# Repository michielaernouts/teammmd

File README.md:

# Ambient Intelligence Project
Team MMD

Members:

Michiel Aernouts, Mats De Meyer, Dennis Joosens

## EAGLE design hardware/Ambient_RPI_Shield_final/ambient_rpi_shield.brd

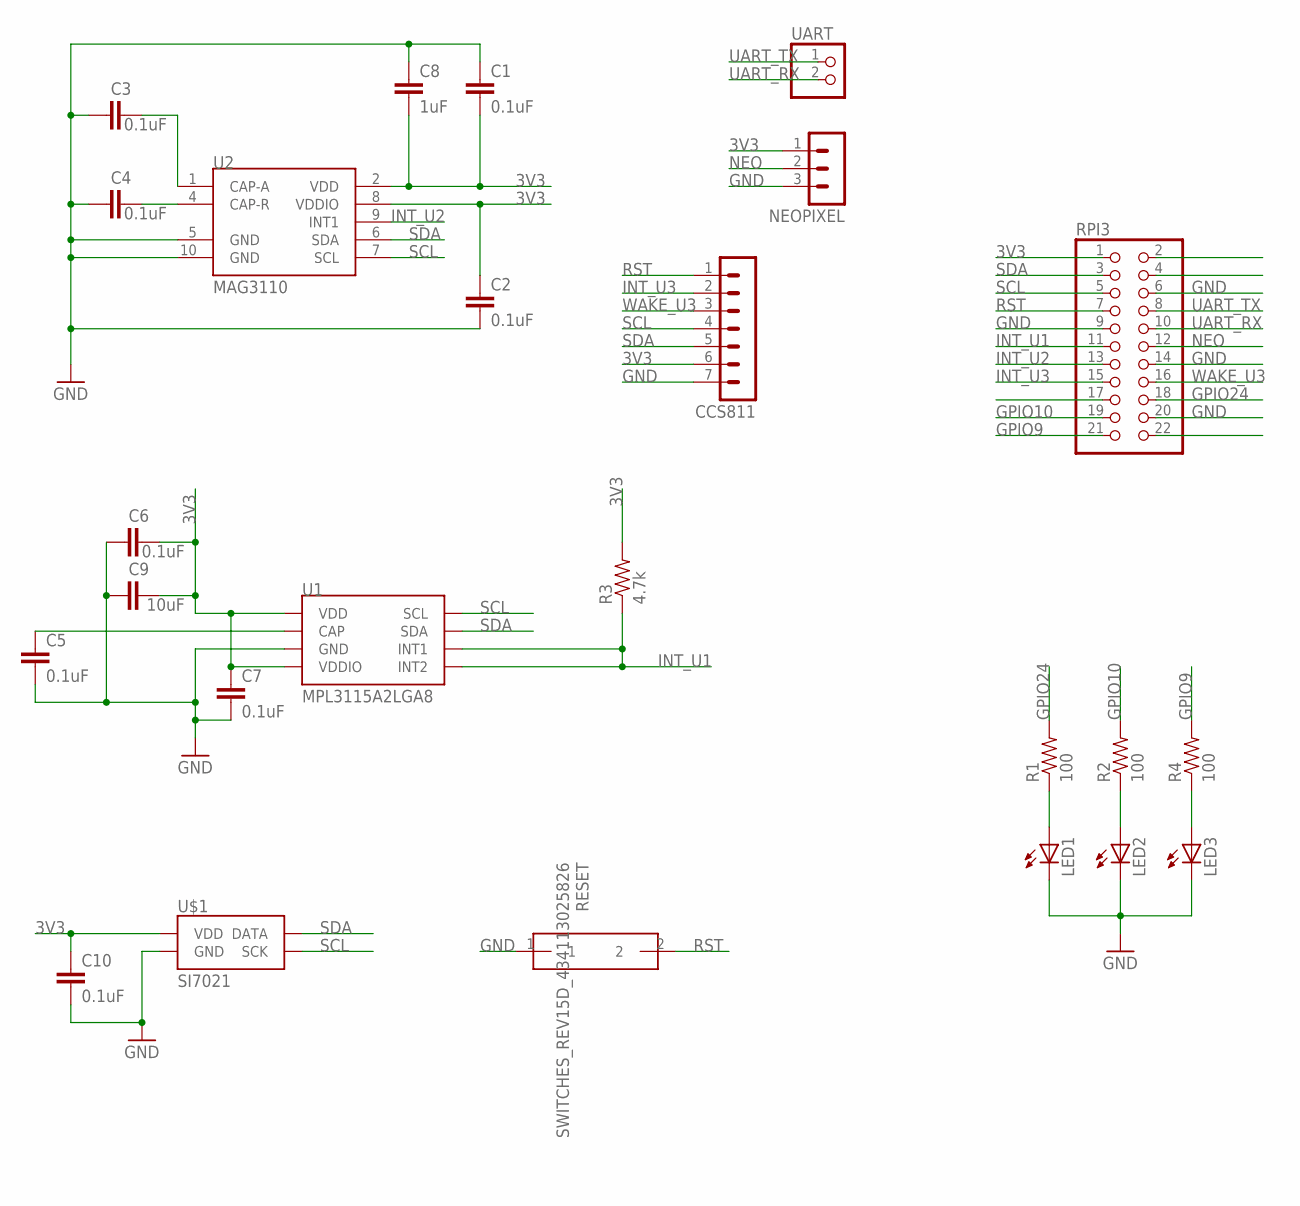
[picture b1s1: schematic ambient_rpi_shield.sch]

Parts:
C1, C2, C3, C4, C5, C6, C7, C10: 0.1uF; 0603-CAP
C8: 1uF; 0603-CAP
C9: 10uF; 0603-CAP
CCS811: MA07-1
LED1, LED2: LED_LEDCHIP-LED0805; LED_CHIP-LED0805
LED3: LED_LEDCHIP-LED0603; LED_CHIP-LED0603
NEOPIXEL: MA03-1
R1, R2, R4: 100; SPARKFUN_0603-RES
R3: 4.7k; 0603-RES
RESET: SWITCHES_REV15D_434113025826
RPI3: PINHD-2X11; 2X11
U1: MPL3115A2LGA8; LGA8
U2: MAG3110; DFN-10
U$1: SI7021
UART: PINHD-1X2; 1X02

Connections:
3V3: C1.2, C2.1, C6.2, C7.1, C8.2, C9.2, C10.1, CCS811.6, NEOPIXEL.1, R3.2, RPI3.1, U1.1 (VDD), U1.4 (VDDIO), U2.2 (VDD), U2.8 (VDDIO), U$1.VDD
GND: C1.1, C2.2, C3.1, C4.1, C5.2, C6.1, C7.2, C8.1, C9.1, C10.2, CCS811.7, LED1.C, LED2.C, LED3.C, NEOPIXEL.3, RESET.1, RPI3.6, RPI3.9, RPI3.14, RPI3.20, U1.3 (GND), U2.5 (GND), U2.10 (GND), U$1.GND
GPIO9: R4.2, RPI3.21
GPIO10: R2.2, RPI3.19
GPIO24: R1.2, RPI3.18
INT_U1: R3.1, RPI3.11, U1.5 (INT2), U1.6 (INT1)
INT_U2: RPI3.13, U2.9 (INT1)
INT_U3: CCS811.2, RPI3.15
unnamed: C3.2, U2.1 (CAP-A)
unnamed: C4.2, U2.4 (CAP-R)
unnamed: C5.1, U1.2 (CAP)
unnamed: LED1.A, R1.1
unnamed: LED2.A, R2.1
unnamed: LED3.A, R4.1
NEO: NEOPIXEL.2, RPI3.12
RST: CCS811.1, RESET.2, RPI3.7
SCL: CCS811.4, RPI3.5, U1.8 (SCL), U2.7 (SCL), U$1.SCK
SDA: CCS811.5, RPI3.3, U1.7 (SDA), U2.6 (SDA), U$1.DATA
UART_RX: RPI3.10, UART.2
UART_TX: RPI3.8, UART.1
WAKE_U3: CCS811.3, RPI3.16

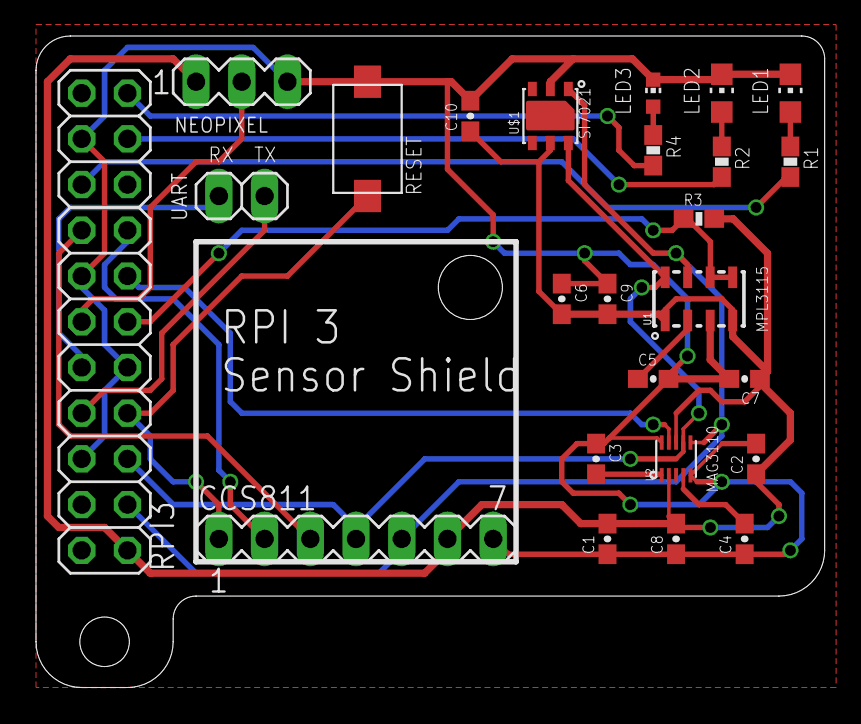
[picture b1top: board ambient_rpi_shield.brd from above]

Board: 2 copper layers, 43.8 x 36.2 mm, 25 parts (0 on the bottom side), 21 nets.

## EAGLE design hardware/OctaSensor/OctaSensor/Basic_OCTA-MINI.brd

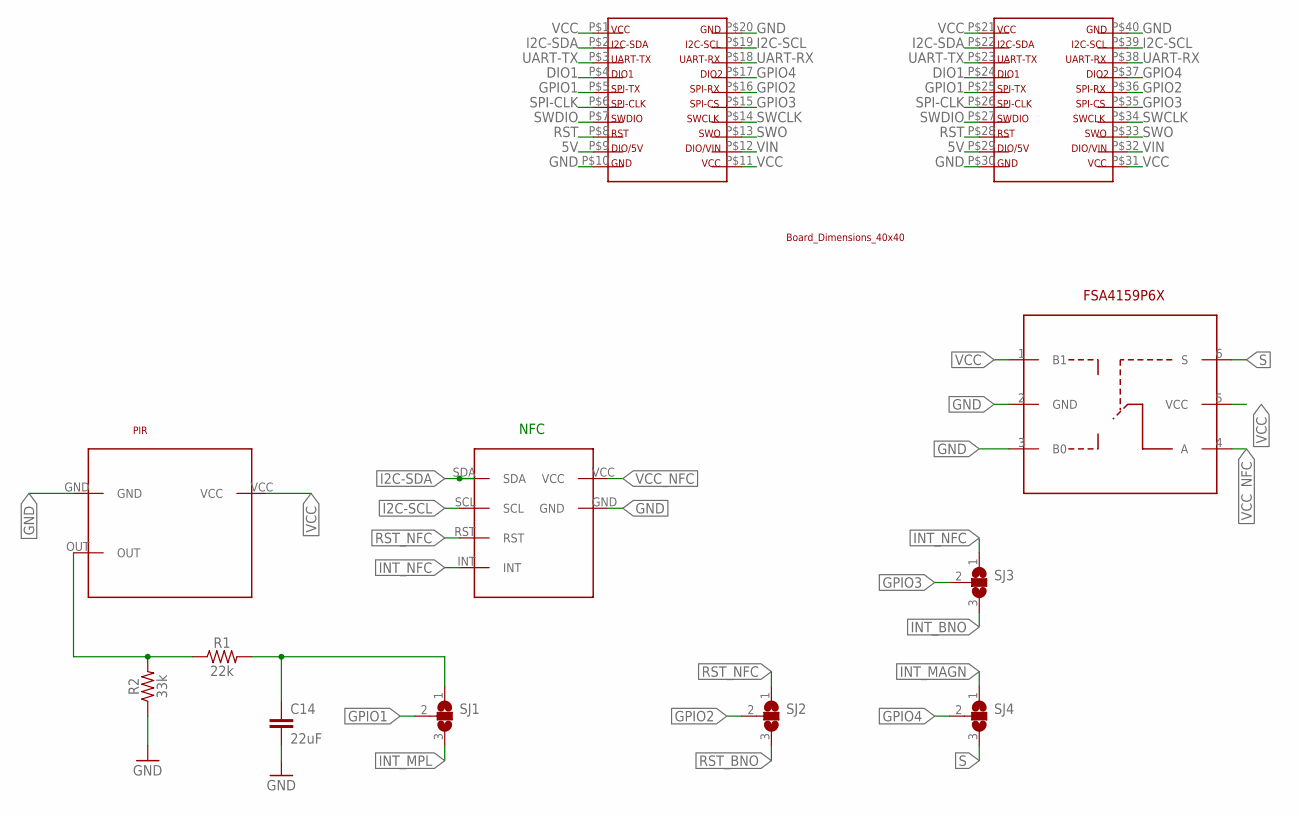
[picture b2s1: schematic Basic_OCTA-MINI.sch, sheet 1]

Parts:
C14: 22uF; 0805
R1: 22k; 0603
R2: 33k; 0603
SJ1, SJ2, SJ3, SJ4: SJ2W; SJ_2
U$2: BOARD-DIMENSIONS-40X40
U$9: PIR
U$10: NFC
U$17: FSA4159P6X; SOT65P210X100-6N

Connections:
5V: U$2.P$9, U$2.P$29
DIO1: U$2.P$4, U$2.P$24
GND: C14.2, R2.1, U$2.P$10, U$2.P$20, U$2.P$30, U$2.P$40, U$9.GND, U$10.GND, U$17.2 (GND), U$17.3 (B0); also elsewhere on the board
GPIO1: SJ1.2, U$2.P$5, U$2.P$25
GPIO2: SJ2.2, U$2.P$16, U$2.P$36
GPIO3: SJ3.2, U$2.P$15, U$2.P$35
GPIO4: SJ4.2, U$2.P$17, U$2.P$37
I2C-SCL: U$2.P$19, U$2.P$39, U$10.SCL; also elsewhere on the board
I2C-SDA: U$2.P$2, U$2.P$22, U$10.SDA; also elsewhere on the board
INT_BNO: SJ3.3; also elsewhere on the board
INT_MAGN: SJ4.1; also elsewhere on the board
INT_MPL: SJ1.3; also elsewhere on the board
INT_NFC: SJ3.1, U$10.INT
unnamed: R1.1, R2.2, U$9.OUT
OUT2_PIR: C14.1, R1.2, SJ1.1
RST: U$2.P$8, U$2.P$28
RST_BNO: SJ2.3; also elsewhere on the board
RST_NFC: SJ2.1, U$10.RST
S: SJ4.3, U$17.6 (S)
SPI-CLK: U$2.P$6, U$2.P$26
SWCLK: U$2.P$14, U$2.P$34
SWDIO: U$2.P$7, U$2.P$27
SWO: U$2.P$13, U$2.P$33
UART-RX: U$2.P$18, U$2.P$38
UART-TX: U$2.P$3, U$2.P$23
VCC: U$2.P$1, U$2.P$11, U$2.P$21, U$2.P$31, U$9.VCC, U$17.1 (B1), U$17.5 (VCC); also elsewhere on the board
VCC_NFC: U$10.VCC, U$17.4 (A)
VIN: U$2.P$12, U$2.P$32

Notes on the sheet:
NFC

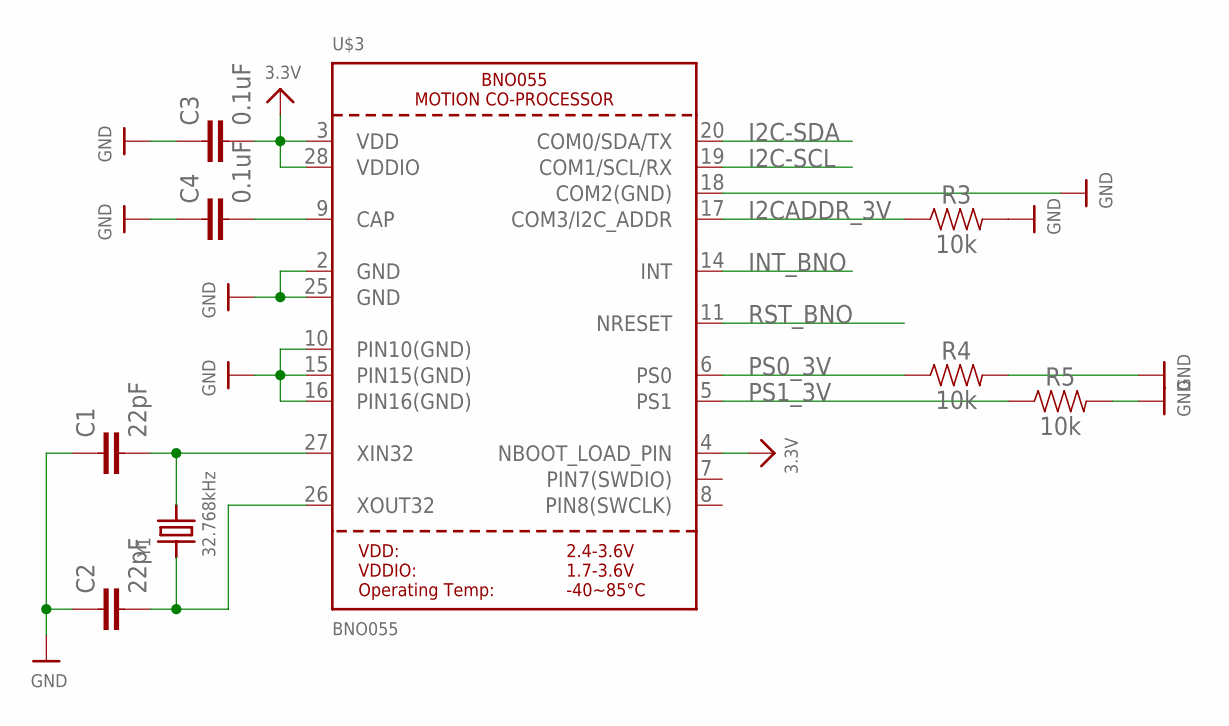
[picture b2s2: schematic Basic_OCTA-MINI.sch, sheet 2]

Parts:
C1, C2: 22pF; 0603
C3, C4: 0.1uF; 0603
R3, R4, R5: 10k; 0603
U$3: BNO055
Y1: 32.768kHz; CRYSTAL_8X3.8

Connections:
GND: C1.1, C2.1, C3.1, C4.1, R3.2, R4.2, R5.2, U$3.2 (GND), U$3.10 (PIN10(GND)), U$3.15 (PIN15(GND)), U$3.16 (PIN16(GND)), U$3.18 (COM2(GND)), U$3.25 (GND); also elsewhere on the board
I2C-SCL: U$3.19 (COM1/SCL/RX); also elsewhere on the board
I2C-SDA: U$3.20 (COM0/SDA/TX); also elsewhere on the board
I2CADDR_3V: R3.1, U$3.17 (COM3/I2C_ADDR)
INT_BNO: U$3.14 (INT); also elsewhere on the board
unnamed: C1.2, U$3.27 (XIN32), Y1.P$4 (2)
unnamed: C2.2, U$3.26 (XOUT32), Y1.P$1 (1)
unnamed: C4.2, U$3.9 (CAP)
PS0_3V: R4.1, U$3.6 (PS0)
PS1_3V: R5.1, U$3.5 (PS1)
RST_BNO: U$3.11 (NRESET); also elsewhere on the board
VCC: C3.2, U$3.3 (VDD), U$3.4 (NBOOT_LOAD_PIN), U$3.28 (VDDIO); also elsewhere on the board

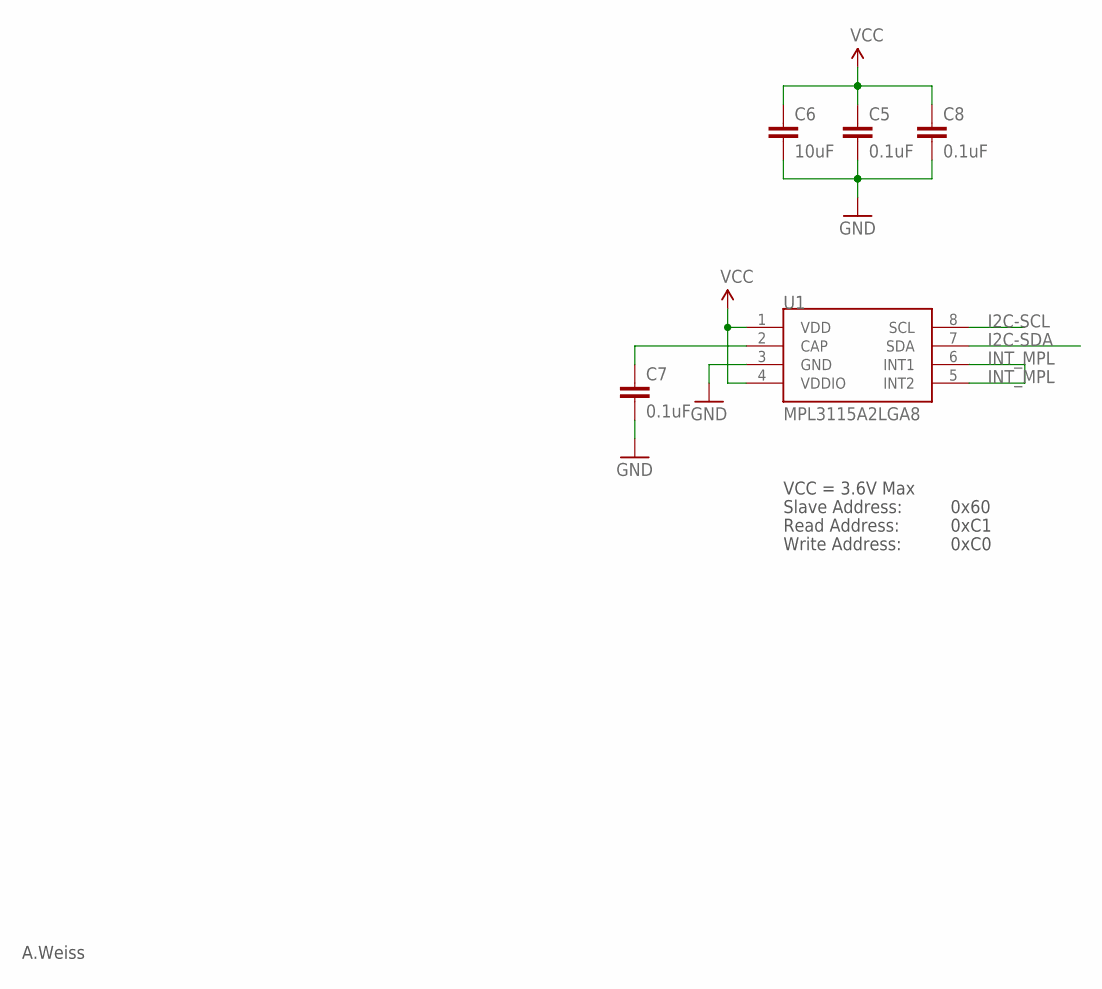
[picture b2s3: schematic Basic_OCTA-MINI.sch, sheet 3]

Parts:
C5, C7, C8: 0.1uF; 0603
C6: 10uF; 0603
U1: MPL3115A2LGA8; LGA8

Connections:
GND: C5.2, C6.2, C7.2, C8.2, U1.3 (GND); also elsewhere on the board
I2C-SCL: U1.8 (SCL); also elsewhere on the board
I2C-SDA: U1.7 (SDA); also elsewhere on the board
INT_MPL: U1.5 (INT2), U1.6 (INT1); also elsewhere on the board
unnamed: C7.1, U1.2 (CAP)
VCC: C5.1, C6.1, C8.1, U1.1 (VDD), U1.4 (VDDIO); also elsewhere on the board

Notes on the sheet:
A.Weiss
VCC = 3.6V Max
Read Address:
Write Address:
Slave Address:
0x60
0xC1
0xC0

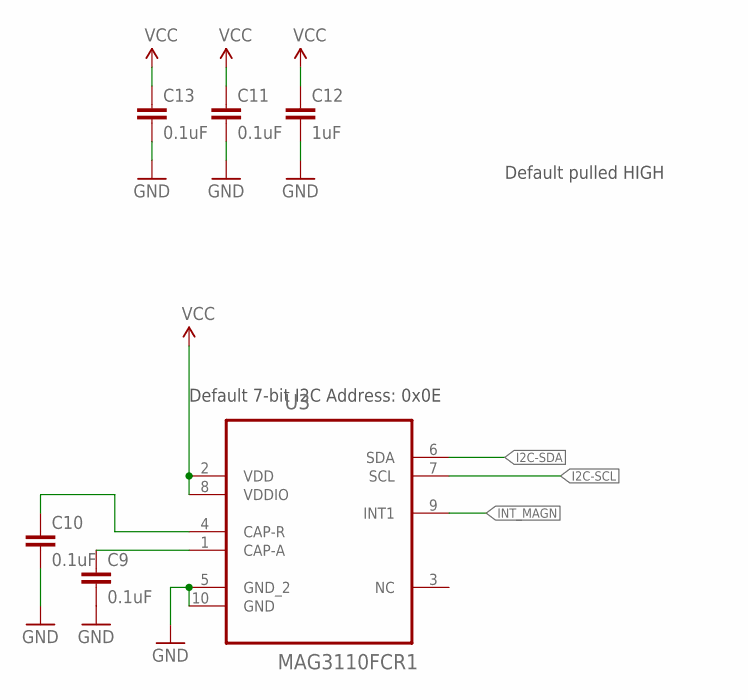
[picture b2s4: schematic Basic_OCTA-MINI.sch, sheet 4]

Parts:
C9, C10, C11, C13: 0.1uF; 0603-CAP
C12: 1uF; 0603-CAP
U3: MAG3110FCR1; DFN200X200X90-10N

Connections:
GND: C9.2, C10.2, C11.2, C12.2, C13.2, U3.5 (GND_2), U3.10 (GND); also elsewhere on the board
I2C-SCL: U3.7 (SCL); also elsewhere on the board
I2C-SDA: U3.6 (SDA); also elsewhere on the board
INT_MAGN: U3.9 (INT1); also elsewhere on the board
unnamed: C10.1, U3.4 (CAP-R)
unnamed: C9.1, U3.1 (CAP-A)
VCC: C11.1, C12.1, C13.1, U3.2 (VDD), U3.8 (VDDIO); also elsewhere on the board

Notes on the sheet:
Default pulled HIGH
Default 7-bit I2C Address: 0x0E

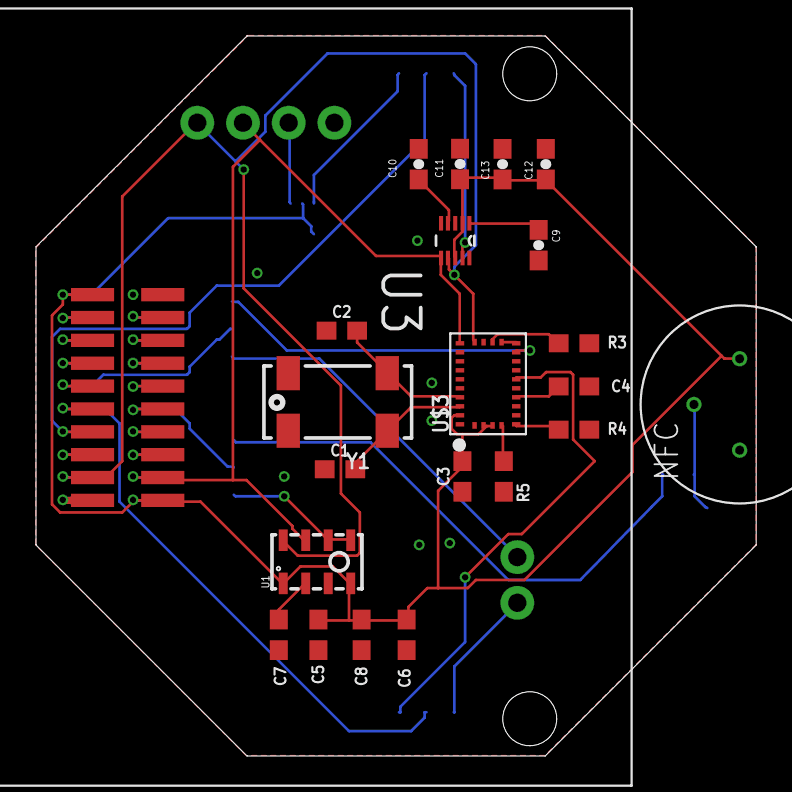
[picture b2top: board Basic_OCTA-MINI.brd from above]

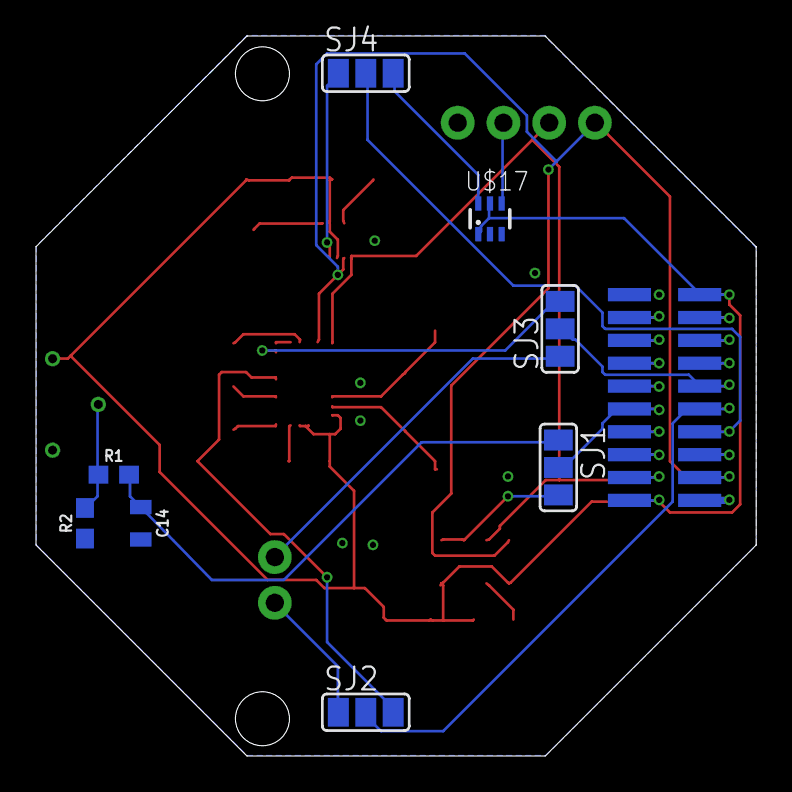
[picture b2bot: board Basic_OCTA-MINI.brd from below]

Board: 2 copper layers, 40.0 x 40.0 mm, 31 parts (8 on the bottom side), 37 nets.

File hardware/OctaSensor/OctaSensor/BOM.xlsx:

Description | Value | Parts | Package | # per board | Ordernummer | Website
Capacitor | 0.1uF | C9, C10, C11, C13,C3, C4, C5, C7 | 0603-CAP | 9 | 1759016 | farnell
1µF ceramic capacitors | 1.0uF | C8,C12 | 0603-CAP | 1 | 1759399 | farnell
10µF ceramic capacitors | 10uF | C6 | 0603-CAP | 1 | 2494233 | farnell
22pF ceramic capacitors | 22pF | C1, C2 | 0603-CAP | 2 | 9406107 | farnell
22µF ceramic capacitors | 22uF | C14 | 8050-CAP | 1 | 1759415 | farnell
33kΩ resistor | 33k | R2 | 0603-CAP | 1 | 2447342 | farnell
10kΩ resistor | 10k | R3, R4, R5 | 0603-CAP | 3 | 2447230 | farnell
22kΩ resistor | 22k | R1 | 0603-CAP | 1 | 2073430 | farnell
Crystals | 32.768kHz | Y1 | CRYSTAL_8X3.8 | 1 | 1611824 | farnell
Analogue Switch | FSA4159P6X | U$17 | SOT65P210X100-6N | 1 | 1495462 | farnell
MAGNETOMETER | MAG3110FCR1 | U3 | DFN200X200X90-10N | 1 | 2080492 | farnell
Altimeter/Pressure Sensor | MPL3115A2LGA8 | U1 | LGA8 | 1 | 2009084 | farnell
BNO055 - Motion Co-Processor | BNO055 | U$3 | BNO055 | 1 | 262-BNO055 | mouser

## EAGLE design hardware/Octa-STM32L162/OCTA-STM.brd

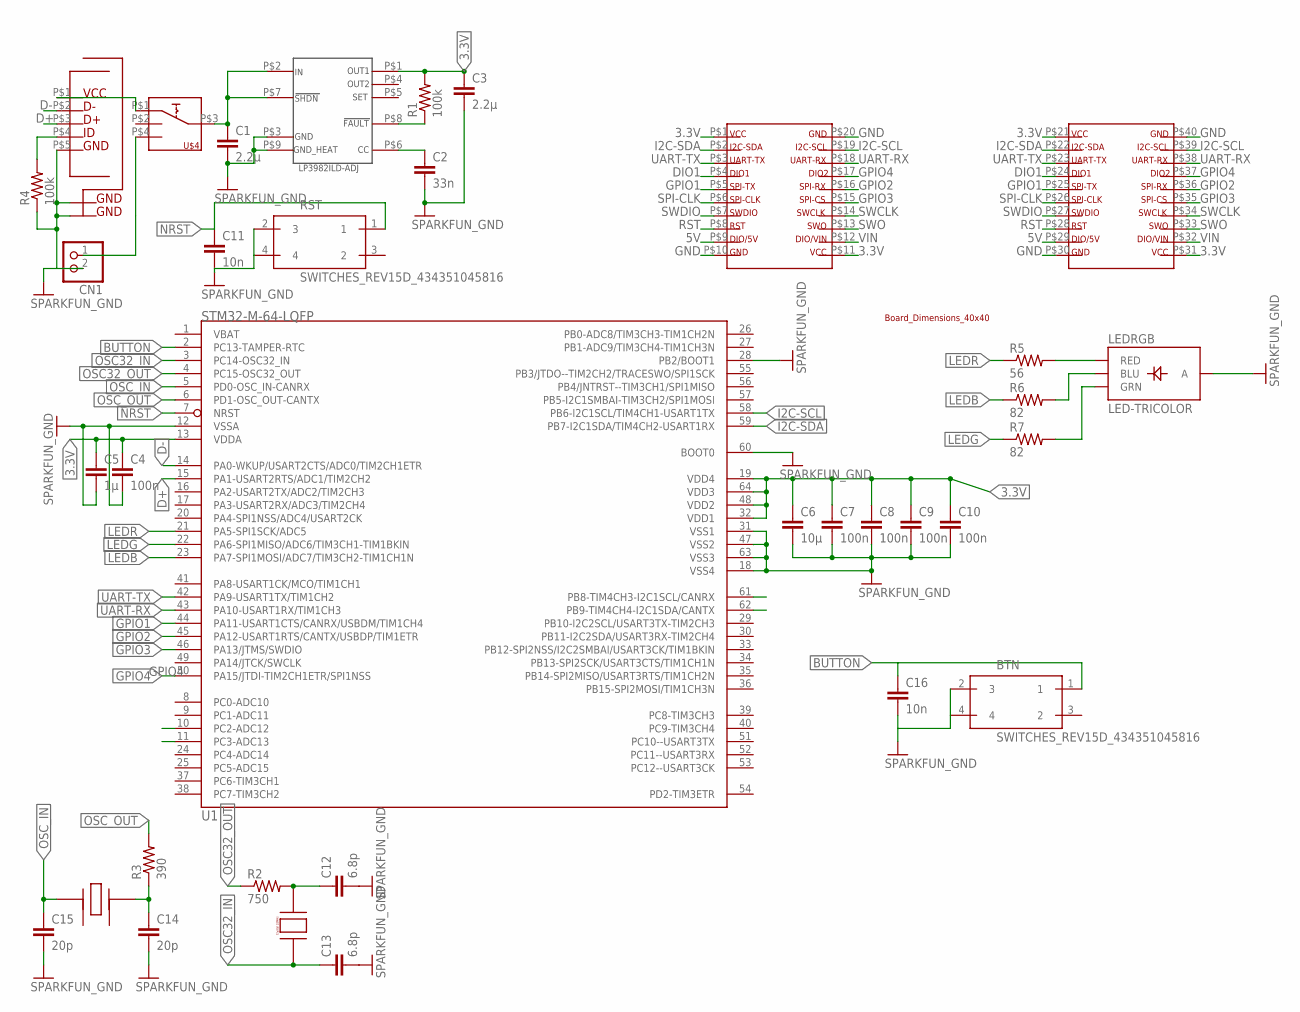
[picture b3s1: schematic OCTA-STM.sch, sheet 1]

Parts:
BTN: SWITCHES_REV15D_434351045816
C1, C3: 2.2µ; SPARKFUN_0603-CAP
C2: 33n; SPARKFUN_0603-CAP
C4, C7, C8, C9, C10: 100n; SPARKFUN_0603-CAP
C5: 1µ; SPARKFUN_0603-CAP
C6: 10µ; SPARKFUN_0603-CAP
C11, C16: 10n; SPARKFUN_0603-CAP
C12, C13: 6.8p; SPARKFUN_0603-CAP
C14, C15: 20p; SPARKFUN_0603-CAP
CN1: ADAFRUIT_JST_2PIN-SMT-RA; ADAFRUIT_JST-PH-2-SMT-RA
LEDRGB: LED-TRICOLOR; LED-TRICOLOR-SMD
R1, R4: 100k; SPARKFUN_0603-RES
R2: 750; SPARKFUN_0603-RES
R3: 390; SPARKFUN_0603-RES
R5: 56; SPARKFUN_0603-RES
R6, R7: 82; SPARKFUN_0603-RES
RST: SWITCHES_REV15D_434351045816
U1: STM32-M-64-LQFP; LQFP64
U$1: OCTA-CORE_MCIRO-USB2; OCTA-CORE_MICRO-USB2
U$2: BOARD-DIMENSIONS-40X40
U$3: DRAGAN-PERSONAL_TI-3.3V-REGULATOR
U$4: OCTA-CORE_SP3T
U$5: DRAGAN-PERSONAL_CRYSTAL_32MHZ
U$7: DRAGAN-PERSONAL_XTAL-26MHZ

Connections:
3.3V: C3.1, C4.1, C5.1, C6.1, C7.1, C8.1, C9.1, C10.1, R1.2, U1.13 (VDDA), U1.19 (VDD4), U1.32 (VDD1), U1.48 (VDD2), U1.64 (VDD3), U$2.P$1, U$2.P$11, U$2.P$21, U$2.P$31, U$3.P$1
5V: U$2.P$9, U$2.P$29
10: U1.10 (PC2-ADC12)
11: U1.11 (PC3-ADC13)
61: U1.61 (PB8-TIM4CH3-I2C1SCL/CANRX)
62: U1.62 (PB9-TIM4CH4-I2C1SDA/CANTX)
BUTTON: BTN.1, C16.1, U1.2 (PC13-TAMPER-RTC)
D+: U1.15 (PA1-USART2RTS/ADC1/TIM2CH2), U$1.P$3
D-: U1.14 (PA0-WKUP/USART2CTS/ADC0/TIM2CH1ETR), U$1.P$2
DIO1: U$2.P$4, U$2.P$24
GND: BTN.2 (3), BTN.4, C1.2, C2.2, C3.2, C4.2, C5.2, C6.2, C7.2, C8.2, C9.2, C10.2, C11.2, C12.2, C13.2, C14.2, C15.2, C16.2, CN1.2 (1), LEDRGB.A, R4.1, RST.2 (3), RST.4, U1.12 (VSSA), U1.18 (VSS4), U1.28 (PB2/BOOT1), U1.31 (VSS1), U1.47 (VSS2), U1.60 (BOOT0), U1.63 (VSS3), U$1.P$5, U$1.P$6, U$1.P$7, U$1.P$8, U$1.P$9, U$1.P$10, U$1.P$11, U$1.P$12, U$1.P$13, U$2.P$10, U$2.P$20, U$2.P$30, U$2.P$40, U$3.P$3, U$3.P$9; also elsewhere on the board
GPIO1: U1.44 (PA11-USART1CTS/CANRX/USBDM/TIM1CH4), U$2.P$5, U$2.P$25
GPIO2: U1.45 (PA12-USART1RTS/CANTX/USBDP/TIM1ETR), U$2.P$16, U$2.P$36
GPIO3: U1.46 (PA13/JTMS/SWDIO), U$2.P$15, U$2.P$35
GPIO4: U1.50 (PA15/JTDI-TIM2CH1ETR/SPI1NSS), U$2.P$17, U$2.P$37
I2C-SCL: U1.58 (PB6-I2C1SCL/TIM4CH1-USART1TX), U$2.P$19, U$2.P$39
I2C-SDA: U1.59 (PB7-I2C1SDA/TIM4CH2-USART1RX), U$2.P$2, U$2.P$22
LEDB: R6.1, U1.23 (PA7-SPI1MOSI/ADC7/TIM3CH2-TIM1CH1N)
LEDG: R7.1, U1.22 (PA6-SPI1MISO/ADC6/TIM3CH1-TIM1BKIN)
LEDR: R5.1, U1.21 (PA5-SPI1SCK/ADC5)
unnamed: LEDRGB.R (RED), R5.2
unnamed: LEDRGB.B (BLU), R6.2
unnamed: C1.1, U$3.P$2, U$3.P$7, U$4.P$3
unnamed: C2.1, U$3.P$6
unnamed: C12.1, R2.2, U$5.P$2
unnamed: R1.1, U$3.P$8
unnamed: R4.2, U$1.P$4
unnamed: C14.1, R3.1, U$7.P$3
unnamed: LEDRGB.G (GRN), R7.2
NRST: C11.1, RST.1, U1.7 (NRST)
OSC32_IN: C13.1, U1.3 (PC14-OSC32_IN), U$5.P$3
OSC32_OUT: R2.1, U1.4 (PC15-OSC32_OUT)
OSC_IN: C15.1, U1.5 (PD0-OSC_IN-CANRX), U$7.P$1
OSC_OUT: R3.2, U1.6 (PD1-OSC_OUT-CANTX)
RST: U$2.P$8, U$2.P$28
SPI-CLK: U$2.P$6, U$2.P$26
SWCLK: U$2.P$14, U$2.P$34
SWDIO: U$2.P$7, U$2.P$27
SWO: U$2.P$13, U$2.P$33
UART-RX: U1.43 (PA10-USART1RX/TIM1CH3), U$2.P$18, U$2.P$38
UART-TX: U1.42 (PA9-USART1TX/TIM1CH2), U$2.P$3, U$2.P$23
VIN: U$2.P$12, U$2.P$32
VLIPO: CN1.1 (2), U$4.P$4; also elsewhere on the board
VUSB+: U$1.P$1, U$4.P$1; also elsewhere on the board

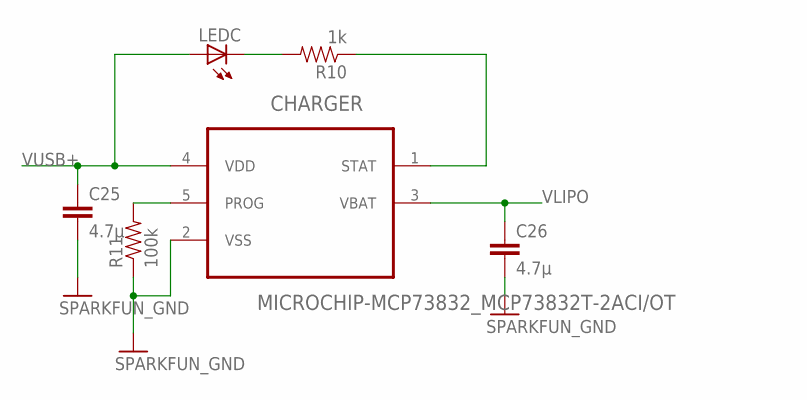
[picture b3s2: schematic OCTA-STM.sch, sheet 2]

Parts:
C25, C26: 4.7µ; SPARKFUN_0603-CAP
CHARGER: MICROCHIP-MCP73832_MCP73832T-2ACI/OT; MICROCHIP-MCP73832_SOT95P280X145-5N
LEDC: LED_LEDCHIP-LED0805; LED_CHIP-LED0805
R10: 1k; SPARKFUN_0603-RES
R11: 100k; SPARKFUN_0603-RES

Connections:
GND: C25.2, C26.2, CHARGER.2 (VSS), R11.1; also elsewhere on the board
unnamed: CHARGER.5 (PROG), R11.2
unnamed: LEDC.C, R10.2
unnamed: CHARGER.1 (STAT), R10.1
VLIPO: C26.1, CHARGER.3 (VBAT); also elsewhere on the board
VUSB+: C25.1, CHARGER.4 (VDD), LEDC.A; also elsewhere on the board

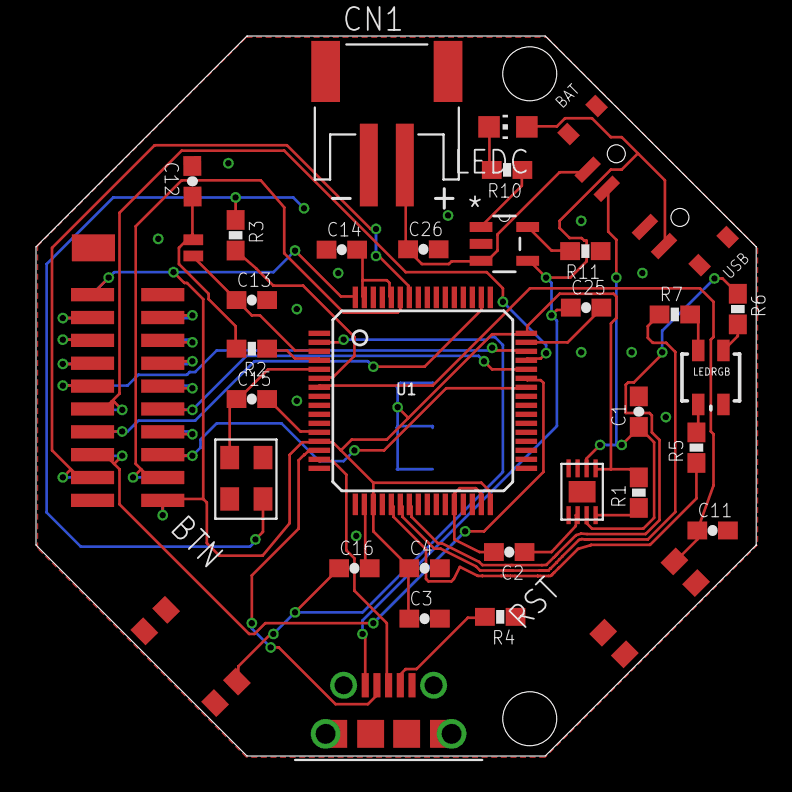
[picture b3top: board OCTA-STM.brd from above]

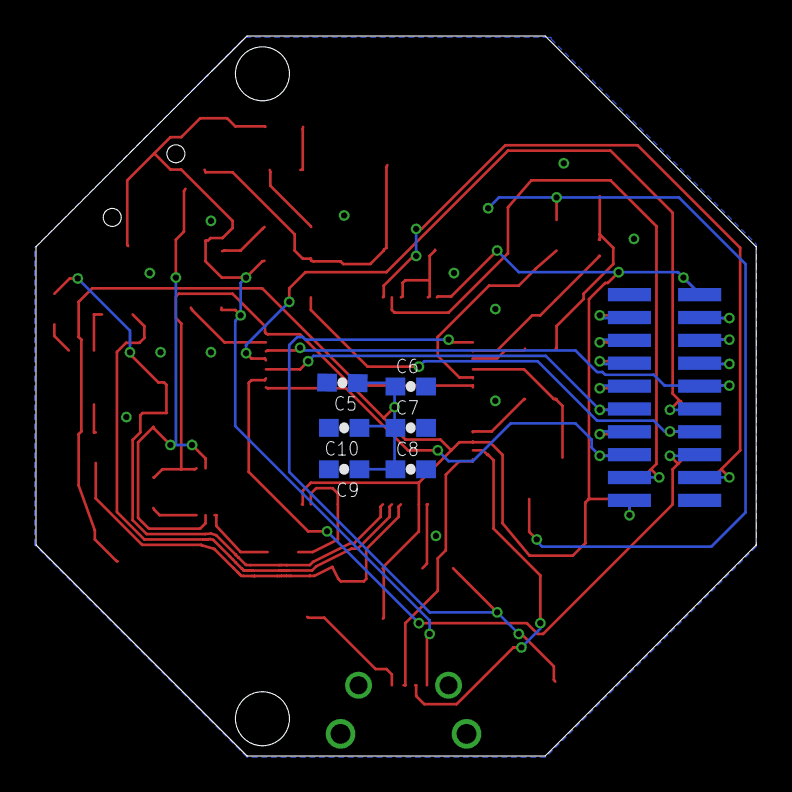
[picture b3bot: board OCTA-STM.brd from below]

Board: 2 copper layers, 40.0 x 40.0 mm, 40 parts (6 on the bottom side), 43 nets.

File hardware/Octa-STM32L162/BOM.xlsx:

Description | Part | Value | Device | Amount/board | Website | Ordernummer
Crystal | 8MHZ | SMD 3,2 x 2,5 mm |  | 1 | Farnell | 2467921RL
Side Push Button | BTN, RST | SWITCHES_REV15D_434351045816 | SWITCHES_REV15D_434351045816 | 2 | Mouser | 667-EVQ-PUA02K
Capacitor | C1, C3 | 2.2µ | SPARKFUN_CAP0603-CAP | 2 | Farnell | 2320817
Capacitor | C2 | 33n | SPARKFUN_CAP0603-CAP | 1 | Farnell | 1759112
Capacitor | C4, C7, C8, C9, C10 | 100n | SPARKFUN_CAP0603-CAP | 5 | Farnell | 1759016
Capacitor | C5 | 1µ | SPARKFUN_CAP0603-CAP | 1 | Farnell | 1759399
Capacitor | C6 | 10µ | SPARKFUN_CAP0603-CAP | 1 | Farnell | 2494233
Capacitor | C11, C16 | 10n | SPARKFUN_CAP0603-CAP | 2 | Farnell | 1759003
Capacitor | C12, C13 | 6.8p | SPARKFUN_CAP0603-CAP | 2 | Farnell | 2627470
Capacitor | C14, C15 | 20p | SPARKFUN_CAP0603-CAP | 2 | Farnell | 2627461
Capacitor | C25, C26 | 4.7µ | SPARKFUN_CAP0603-CAP | 2 | Farnell | 2112741
Charge Management Controller | CHARGER | MICROCHIP-MCP73832_MCP73832T-2ACI/OT | MICROCHIP-MCP73832_MCP73832T-2ACI/OT | 1 | Farnell | 1332159
JST 2-Pin Connectors of various flavors | CN1 |  | ADAFRUIT_JST_2PIN-SMT-RA | 1 | Mouser | 710-620102131822
LED, green | LEDC |  | LED_LEDCHIP-LED0805 | 1 | Farnell | 2099239
LED, RGB | LEDRGB |  | LED-TRICOLOR | 1 | Mouser | COM-07844
Resistor | R1, R4, R11 | 100k | SPARKFUN_RESISTOR0603-RES | 3 | Farnell | 2309107
Resistor | R2 | 750 | SPARKFUN_RESISTOR0603-RES | 1 | Farnell | 2059597
Resistor | R3 | 390 | SPARKFUN_RESISTOR0603-RES | 1 | Farnell | 2502455
Resistor | R5 | 56 | SPARKFUN_RESISTOR0603-RES | 1 | Farnell | 2502469
Resistor | R6, R7 | 82 | SPARKFUN_RESISTOR0603-RES |  | Farnell | 2502484
Resistor | R10 | 1k | SPARKFUN_RESISTOR0603-RES | 1 | Farnell | 2447272RL
MICRO USB | U$1 | OCTA-CORE_MCIRO-USB2 | OCTA-CORE_MCIRO-USB2 | 1 | Mouser | 649-10118194-0001LF
Header (bottom) |  |  |  | 1 | Mouser | 649-202132100020C4LF
Header (top) | U$2 | BOARD-DIMENSIONS-40X40 | BOARD-DIMENSIONS-40X40 | 1 | Mouser | 649-202112100020C4LF
Voltage Regulator 3,3V | U$3 | DRAGAN-PERSONAL_TI-3.3V-REGULATOR | DRAGAN-PERSONAL_TI-3.3V-REGULATOR | 1 | Mouser | 926-LP3982ILDADJNOPB
Switch | U$4 | OCTA-CORE_SP3T | OCTA-CORE_SP3T | 1 | Mouser | 611-PCM13SMTR
Crystal | U$5 | DRAGAN-PERSONAL_CRYSTAL_32MHZ | DRAGAN-PERSONAL_CRYSTAL_32MHZ | 1 | Mouser | 815-AB26TRQ-32.7-T
STM32L162RDT6 | U1 |  | STM32-LQFP64 | 1 | Farnell | 2333336

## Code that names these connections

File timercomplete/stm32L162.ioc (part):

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Mcu.Name=STM32L162RDTx
Mcu.Package=LQFP64
Mcu.UserName=STM32L162RDTx
PA10.GPIOParameters=GPIO_Label
PA10.GPIO_Label=DASH7RX
PA10.Mode=Asynchronous
PA10.Signal=USART1_RX
PA11.GPIOParameters=GPIO_Label
PA11.GPIO_Label=IPIR_IBAR
PA11.Signal=GPXTI11
PA12.GPIOParameters=GPIO_Label
PA12.GPIO_Label=RSTNFC_RBNO
PA12.Signal=GPIO_Output
PA13.GPIOParameters=GPIO_Label
PA13.GPIO_Label=INFC_IBNO
PA13.Signal=GPIO_Input
PA15.GPIOParameters=GPIO_Label
PA15.GPIO_Label=VNFC
PA15.Signal=GPIO_Output
PA2.GPIOParameters=GPIO_Label
PA2.GPIO_Label=USB_TX
PA2.Mode=Asynchronous
PA2.Signal=USART2_TX
PA3.GPIOParameters=GPIO_Label
PA3.GPIO_Label=USB_RX
PA3.Mode=Asynchronous
PA3.Signal=USART2_RX
PA5.GPIOParameters=PinState,GPIO_Label
PA5.GPIO_Label=LEDG
PA5.PinState=GPIO_PIN_RESET
PA5.Signal=GPIO_Output
PA6.GPIOParameters=GPIO_Label
PA6.GPIO_Label=LEDR
PA6.Signal=GPIO_Output
PA7.GPIOParameters=GPIO_Label
PA7.GPIO_Label=LEDB
PA7.Signal=GPIO_Output
PA9.GPIOParameters=GPIO_Label
PA9.GPIO_Label=DASH7TX
PA9.Mode=Asynchronous
PA9.Signal=USART1_TX
PB6.Mode=I2C
PB6.Signal=I2C1_SCL
PB7.Mode=I2C
PB7.Signal=I2C1_SDA
PC13-WKUP2.GPIOParameters=GPIO_Label
PC13-WKUP2.GPIO_Label=Button
PC13-WKUP2.Signal=GPIO_Input
RCC.HSE_VALUE=24000000
RCC.SYSCLKFreq_VALUE=2097000
board=stm32L162

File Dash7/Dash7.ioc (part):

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Mcu.Name=STM32L152RETx
Mcu.Package=LQFP64
Mcu.UserName=STM32L152RETx
PA10.Mode=Asynchronous
PA10.Signal=USART1_RX
PA13.GPIOParameters=GPIO_Label
PA13.GPIO_Label=TMS
PA13.Signal=SYS_JTMS-SWDIO
PA14.GPIOParameters=GPIO_Label
PA14.GPIO_Label=TCK
PA14.Signal=SYS_JTCK-SWCLK
PA2.GPIOParameters=GPIO_Label
PA2.GPIO_Label=USART_TX
PA2.Mode=Asynchronous
PA2.Signal=USART2_TX
PA3.GPIOParameters=GPIO_Label
PA3.GPIO_Label=USART_RX
PA3.Mode=Asynchronous
PA3.Signal=USART2_RX
PA5.GPIOParameters=GPIO_Label
PA5.GPIO_Label=LD2 [Green Led]
PA5.Signal=GPIO_Output
PA9.Mode=Asynchronous
PA9.Signal=USART1_TX
PB3.GPIOParameters=GPIO_Label
PB3.GPIO_Label=SWO
PB3.Signal=SYS_JTDO-TRACESWO
PB6.Mode=I2C
PB6.Signal=I2C1_SCL
PB7.Mode=I2C
PB7.Signal=I2C1_SDA
PC13-WKUP2.GPIOParameters=GPIO_Label
PC13-WKUP2.GPIO_Label=B1 [Blue PushButton]
PC13-WKUP2.Signal=GPIO_Input
PC14-OSC32_IN.Signal=RCC_OSC32_IN
PC15-OSC32_OUT.Signal=RCC_OSC32_OUT
PH0-OSC_IN.Signal=RCC_OSC_IN
PH1-OSC_OUT.Signal=RCC_OSC_OUT
RCC.HSE_VALUE=8000000
RCC.SYSCLKFreq_VALUE=32000000
RCC.SYSCLKSource=RCC_SYSCLKSOURCE_PLLCLK
board=NUCLEO-L152RE
boardIOC=true

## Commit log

2017-03-22 Committed shell scripts from Rasberry Pi
2017-03-22 Fix GitHub
    Sorry for the fuck-up...
2017-03-22 Organized shell scripts
2017-03-22 added correct acellero and megnato files, not working yet but close
2017-03-22 Added Ambient_Intelligence_TeamMMD.png
2017-03-22 Final version of presentation
2017-03-23 small changes to ppt
2017-03-23 Dash7 project created
2017-03-23 Working dash7 transmit
2017-03-23 Magneto working, PIR almost
2017-03-25 cleanup
2017-03-25 further cleanup
2017-03-26 improved PIR program
2017-03-26 added manuals
2017-03-26 added working (buggy) accelero of mems board and ADXL345 (other accelero)
2017-03-26 removed folder
2017-03-26 readme edited
2017-03-29 PERT Diagram project
2017-03-29 Update PERT Diagram
2017-03-29 Added PERT_Diagram_teammd.xml
2017-04-19 Added RPI Shield design
    Schematic, board and BOM for the RPI shield
2017-04-19 BNO055 project added
    BNO055 project added + minor Dash7 fixes
2017-04-19 Datasheets RPi Shield added
    Datasheets RPi Shield + MEMS Evaluation board added
2017-04-19 working on BNO055
    Dash7 files automatically added to project
2017-04-19 test commit
2017-04-19 Revert "test commit"
    This reverts commit 9d05f47bca53a2271ae507d8d85498a3d60d19fb.
2017-04-19 added cpp library of BNO
2017-04-19 added OCTA PCB's
2017-04-19 restructure of BNO files
2017-04-19 BNO055.h file changed
2017-04-19 BNO055.h changes
2017-04-19 improved BNO library
2017-04-19 I2C fix for BNO05
    All I²C communication was implemented with 'mbed.h' instead of HAL, this
    is now fixed.
2017-04-20 added BNO datasheet
2017-04-20 further changes to BNO library
2017-04-20 Working BNO055 orientation
2017-04-26 added BNO calibration code
2017-04-26 BNO055 Calibration mode
    Sensor starts in calibration mode, when calibration is done a button is
    pressed and the BNO055 is ready for use
2017-04-26 BNO055 automated calibration
2017-04-26 BNO data transmit over Dash7
2017-04-26 Added progress reports week 1 - 8
2017-04-26 Cleanup datasheets
2017-04-27 Added pressure sensor
2017-04-27 Removed temporary files + cleanup in code
2017-04-27 Dash7 updated to transmit variable length
2017-05-03 BOM updated
2017-05-03 RPi backup
    RPi backup from these folders:
    - ~/ambient
    - ~/shell_scripts
    - /etc/openhab2
2017-05-09 added pn532 code
    added pn532 code
2017-05-09 added datasheet PN532
    added datasheet PN532
2017-05-10 new branch
2017-05-10 removed some files
2017-05-10 removed a few files
2017-05-10 edited Read me
2017-05-11 Revert "edited Read me"
    This reverts commit 1498c8d95a0ee1417701e75e8c529c2202c0db96.
2017-05-11 added first merged libs SI7021 and MPL3115A2
    added first merged libs SI7021 and MPL3115A2
2017-05-12 edited README.md
    edited README.md
2017-05-12 edited readme
    edited readme
2017-05-12 edit read me
    edit read me
2017-05-17 added PN532_PIR merge
    added PN532_PIR merge
2017-05-18 Code is ready for Dash7 implementation
    Code is ready for Dash7 implementation
2017-06-08 added code mqtt test2.c
    added code mqtt test2.c
2017-06-08 added power measurements NFC node
2017-06-08 added mag data function
2017-06-09 Added new power measurements for NFC node
2017-06-10 Added localization_map_v317.xml
2017-06-11 Added basic timerinterrupt project
2017-06-11 added new timerproject with other peripherals
2017-06-11 Added rpi_diagram.html
2017-06-12 Added new NFC power measurements
2017-06-12 Added nfc_pir_diagram.html
2017-06-12 Added mobile_node_diagram.html
2017-06-12 Added mobile_node_diagram.png
2017-06-12 Added basic_diagram_teamMMD.html
2017-06-13 mobile node code fix
2017-06-13 Added localization_diagram.html
2017-06-13 Added Mobile Node FLow.xml
2017-06-13 Added NFC Node Flow.xml
2017-06-13 Added localisation_mag_diagram.html
2017-06-14 Added Mobile Node FLow.pdf
2017-06-14 Added NFC Node Flow.pdf
2017-06-14 edit readme
    edit readme
2017-06-14 added FINAL folder
2017-06-14 added screenshots
2017-06-14 Added presentations and progress reports
2017-06-14 added power measurements to final folder

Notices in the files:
parts and their libraries:
SparkFun-Capacitors: Licensing: Creative Commons ShareAlike 4.0 International - https://creativecommons.org/licenses/by-sa/4.0
SparkFun: Licensing: CC v3.0 Share-Alike You are welcome to use this library for commercial purposes.
